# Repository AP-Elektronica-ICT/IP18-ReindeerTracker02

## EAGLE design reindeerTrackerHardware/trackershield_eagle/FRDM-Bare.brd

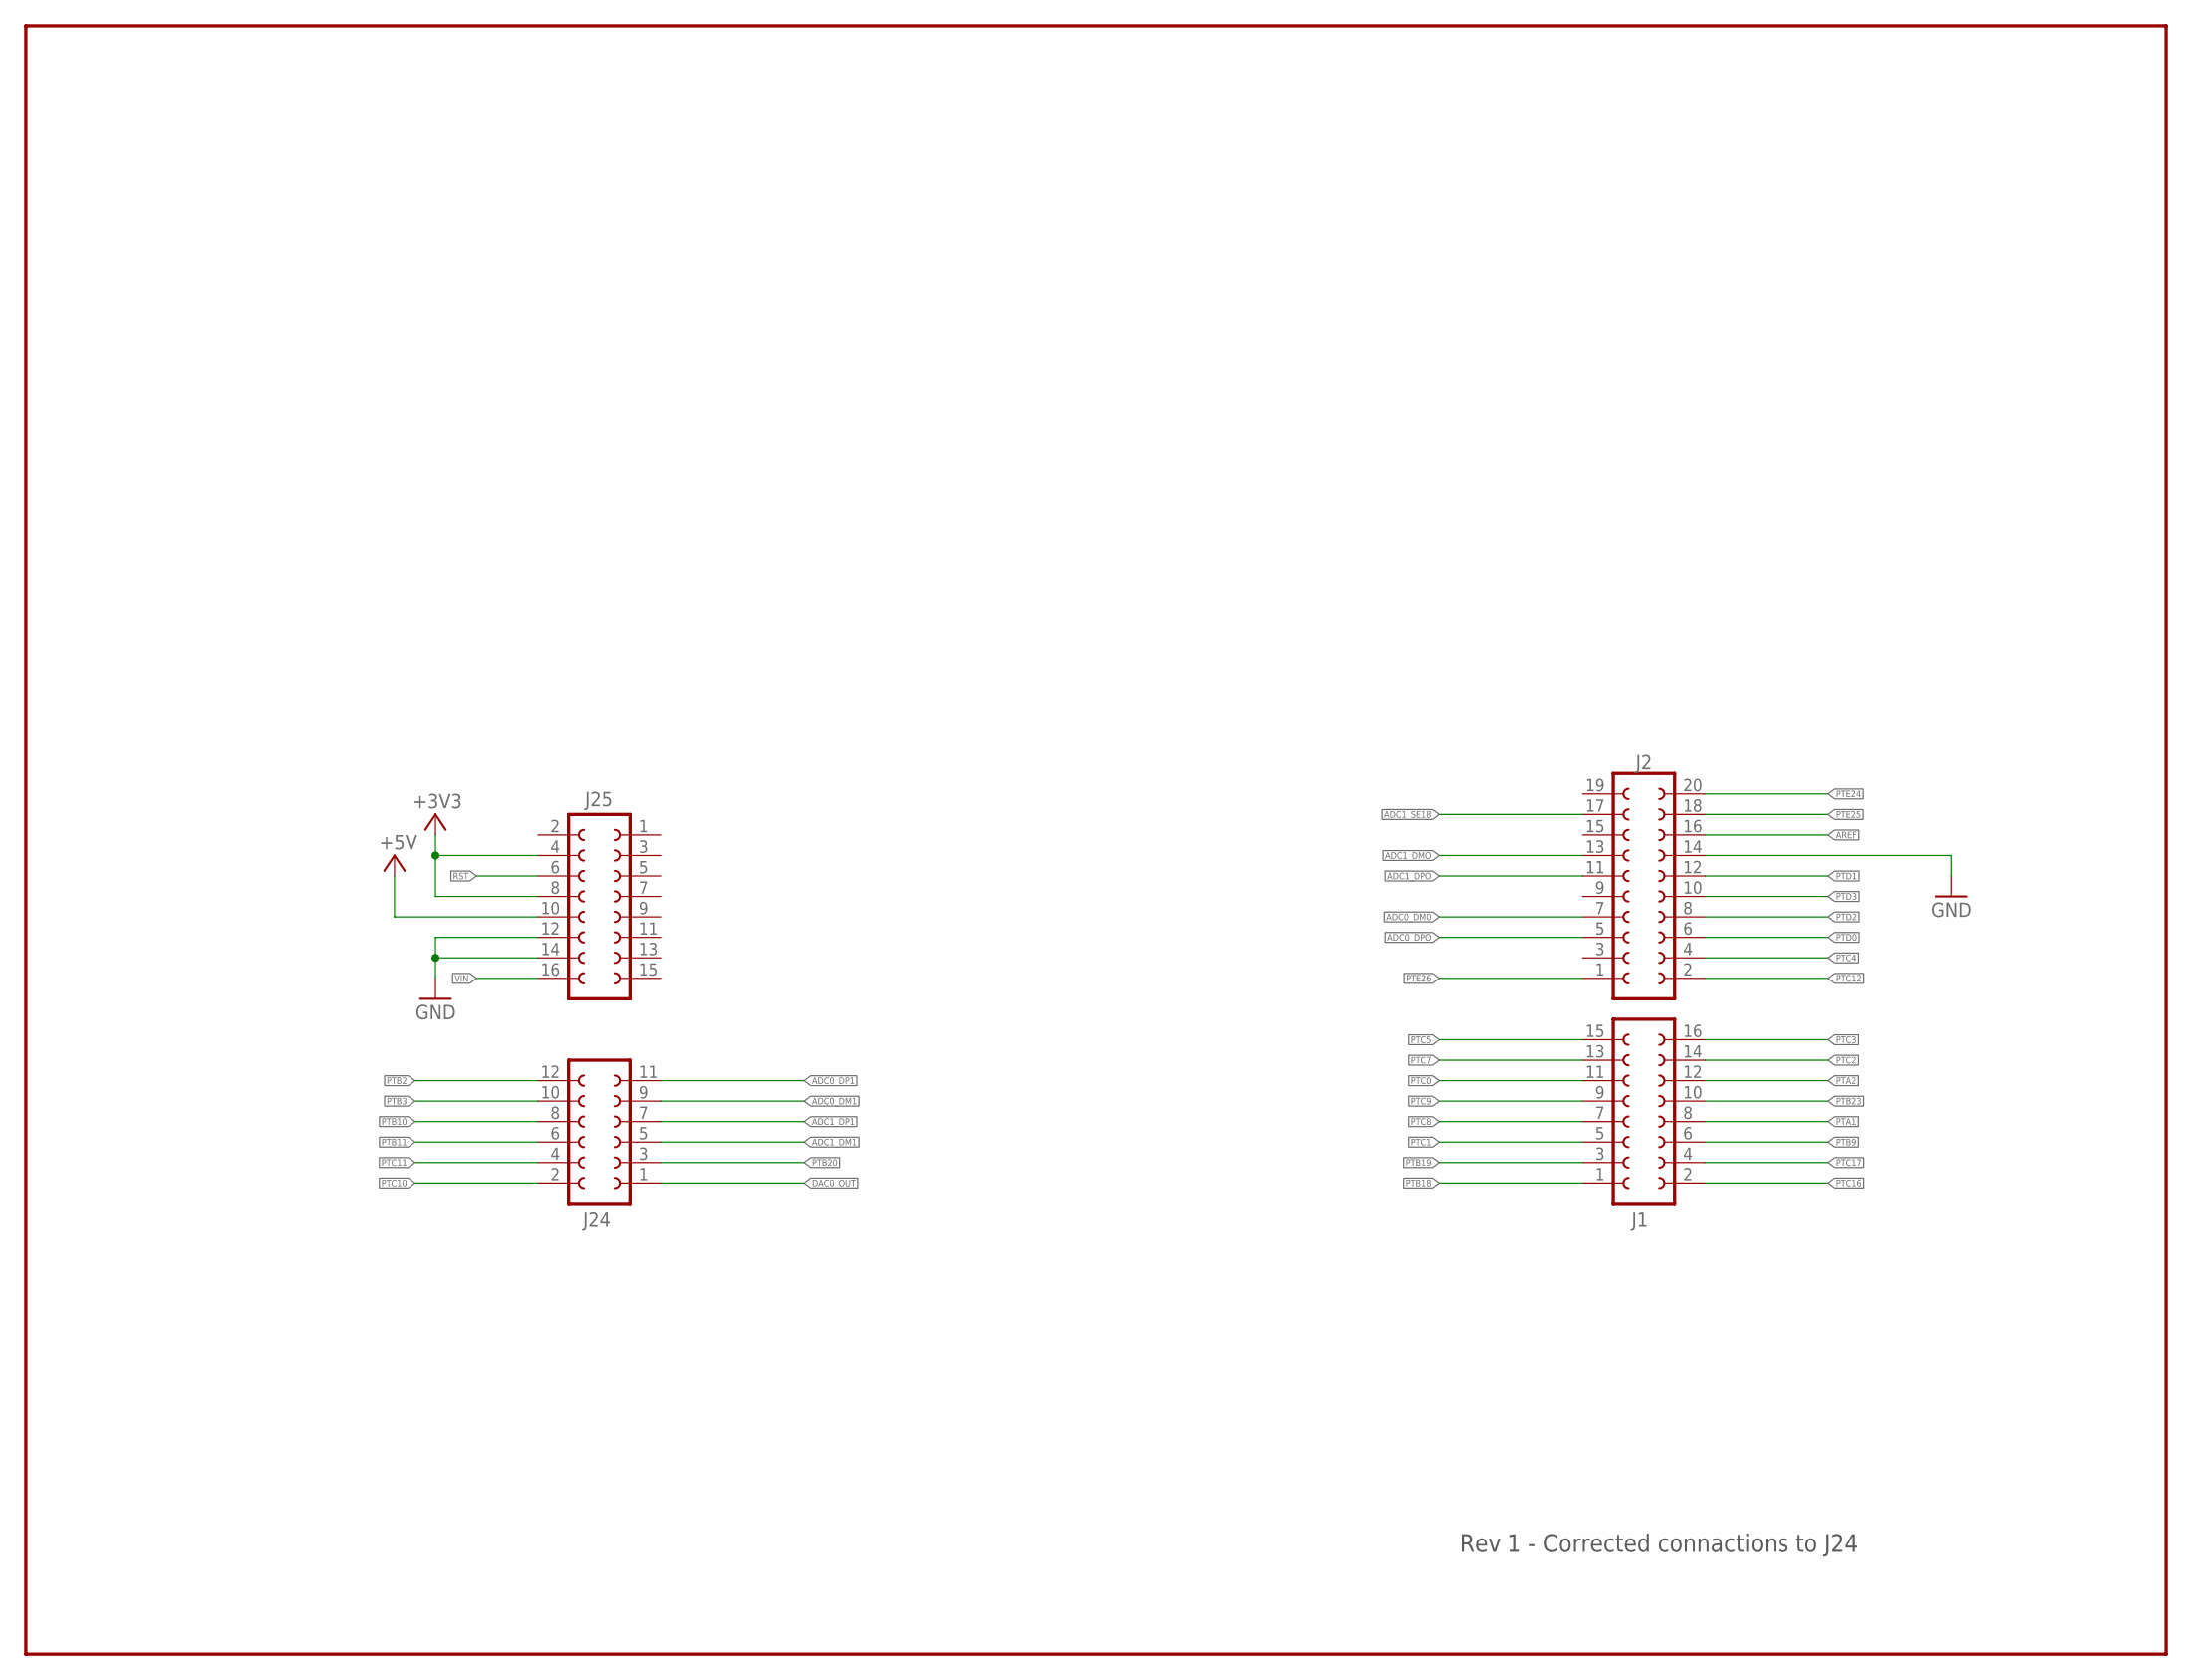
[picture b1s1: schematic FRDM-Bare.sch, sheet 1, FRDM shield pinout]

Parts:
J1, J25: FE08-2
J2: FE10-2
J24: FE06-2

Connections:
+3V3: J25.4, J25.8
+5V: J25.10
ADC0_DM0: J2.7
ADC0_DM1: J24.9
ADC0_DP1: J24.11
ADC0_DPO: J2.5
ADC1_DM1: J24.5
ADC1_DMO: J2.13
ADC1_DP1: J24.7
ADC1_DPO: J2.11
ADC1_SE18: J2.17
AREF: J2.16
DAC0_OUT: J24.1
GND: J2.14, J25.12, J25.14
PTA1: J1.8
PTA2: J1.12
PTB2: J24.12
PTB3: J24.10
PTB9: J1.6
PTB10: J24.8
PTB11: J24.6
PTB18: J1.1
PTB19: J1.3
PTB20: J24.3
PTB23: J1.10
PTC0: J1.11
PTC1: J1.5
PTC2: J1.14
PTC3: J1.16
PTC4: J2.4
PTC5: J1.15
PTC7: J1.13
PTC8: J1.7
PTC9: J1.9
PTC10: J24.2
PTC11: J24.4
PTC12: J2.2
PTC16: J1.2
PTC17: J1.4
PTD0: J2.6
PTD1: J2.12
PTD2: J2.8
PTD3: J2.10
PTE24: J2.20
PTE25: J2.18
PTE26: J2.1
RST: J25.6
VIN: J25.16

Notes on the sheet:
Rev 1 - Corrected connactions to J24

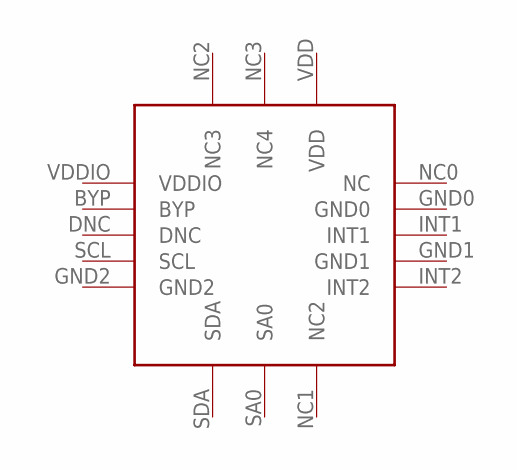
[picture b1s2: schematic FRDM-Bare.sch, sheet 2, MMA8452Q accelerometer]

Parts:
U$1: MMA8452Q; QFNPIN16

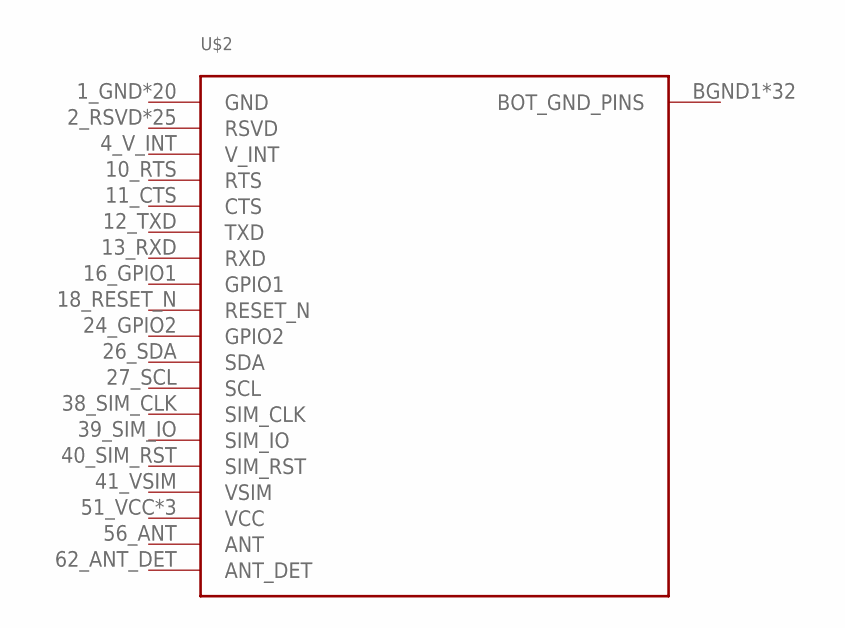
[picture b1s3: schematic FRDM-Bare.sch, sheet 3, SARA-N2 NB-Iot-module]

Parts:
U$2: SARA-N2

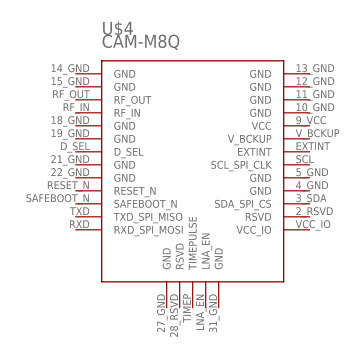
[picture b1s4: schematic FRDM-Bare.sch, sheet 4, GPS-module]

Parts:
U$4: CAM-M8Q

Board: 4 copper layers, 7 parts (0 on the bottom side), 2 nets, no tracks yet.

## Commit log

2018-02-07 Ionic app added
2018-02-07 Angular app added
2018-02-08 Firebase and Bootstrap added
2018-02-08 Serve error fixed
2018-02-08 make directory for hardware team and add datalogger device files
2018-02-08 make new folder reindeerlog for hardware team logging device source code
2018-02-09 make own files for i2c functions
2018-02-09 Updated accelerometer read
2018-02-09 Acc functions moved
2018-02-09 acc read function update
2018-02-09 XYZ axis acceleration reading and printing working
2018-02-09 merge
2018-02-09 acc function update
2018-02-09 paskaA2
2018-02-09 float workkia
2018-02-09 remove saatanan language settings
2018-02-09 start implementin adc
2018-02-11 start doing the SD card part. now can initialize card through SPI
2018-02-11 add FatFs library files
2018-02-12 put back driver files
2018-02-12 put back driver files, more files
2018-02-12 Resolving conflicts
2018-02-12 ADC functions added, working ADC
2018-02-12 Valid key code post call and backend models added
2018-02-12 gitignore added
2018-02-12 Multiple keys error handling and single key add API call added
2018-02-13 Get devices from user added
2018-02-13 Get specific device via deviceKey added
2018-02-13 Committing latest changes
2018-02-13 Return 5 logs with device details
2018-02-13 Get specific logs from device
2018-02-13 User device list only gives last log
2018-02-13 Querys updated, new log stored in first place of array
2018-02-13 Gitignore files/folders removed
2018-02-14 Accelerometer scaled around zero
2018-02-14 2 Accelerometers
2018-02-14 a c c e l b o y s
2018-02-14 SD card finally working yes
2018-02-14 Clean up code and add comments. Now logging reliably for 1,5hr at 25Hz rate
2018-02-15 Temperature sensing added and calibrated coursely
2018-02-15 small improvements
2018-02-16 Homepage website added
2018-02-19 add comments
2018-02-20 Updating
2018-02-20 change board clock settings to achieve lower power
2018-02-20 Interrupt function started, not working yet
2018-02-20 Some updates to SD card drivers to save power
2018-02-21 homepage added
2018-02-22 Routing module added
2018-02-22 basic design of the homescreen of the app
2018-02-22 Backend updated, device contains multiple users
2018-02-22 detail screen basics for app
2018-02-22 sensor service added
2018-02-22 Decreasing power consumpion of FRDM K64F board
2018-02-22 Manifacturers key add page on website added
2018-02-22 minor changes
2018-02-22 Maybe final commit for logger project. Clean up code. Fixed I2C wrong clock source frequency. Slow down data rate to 20hz. Improve sleep mode entering with prepare instruction. Revised external tempe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
2018-02-26 Add trackershield folder
2018-02-26 Version 2 started, acceleration interrupt enabled and working
2018-02-27 add board design files
2018-02-27 Frdm shield layout and components
2018-02-27 Timer counter reset by acceleration interrupt implemented - WIP
2018-02-27 Reindeer details add/update and device activation added on server
2018-02-27 Users can add devices to their list
2018-02-27 users devices display if device is activated
2018-02-27 added add, profile, delete, login and signup page and styled the login page
2018-03-01 Device details get request added to server
2018-03-02 Very low power mode activated
2018-03-02 add more components to trackershield
2018-03-02 make separate lbr file
2018-03-02 nothing useful
2018-03-02 library update
2018-03-02 nothing
2018-03-02 update ignore file to only track source folder
2018-03-02 update another gitignore
2018-03-02 maybe now fixed
2018-03-02 untrack shit..
2018-03-02 rework gitignore file to track ONLY SOURCE FOLDER
2018-03-03 add board folder back to tracked files
2018-03-04 IP11-35 + IP11-38 Detail page added
2018-03-04 activation moved to detail page' q
2018-03-05 detail page styling klaar
2018-03-08 added map to detail page
2018-03-08 login, sign up and password reset added
2018-03-08 Added basic layout to view reindeers of a user
2018-03-11 backand calls added to the app
2018-03-12 Yes.
2018-03-12 small change
2018-03-12 toimitko kiitos
2018-03-12 toimitko kiitos number 2
2018-03-12 paska git
2018-03-12 found the bug that disabled acc-wakeup
2018-03-13 fix ignore file again
2018-03-13 777 the ignore file
2018-03-13 paskaa
2018-03-13 pelastus uritus
2018-03-13 pelasta main
2018-03-13 pelastettu part 2
2018-03-13 New AT-func files added
2018-03-13 modify gitignore again to enable easier new project creation. now it tracks everything except the eclipse conf files(hope so)
2018-03-13 easier project creation still not working. now added .cproject and .project files to git, maybe that fixes it
2018-03-13 now add the files mentioned in previous commit...
2018-03-14 AT-commands communication functions implemented
2018-03-15 Two sided GPS communication by UART implemented
2018-03-15 Added login layout
2018-03-15 userdata on signup added
2018-03-16 Gps func implemented
2018-03-19 GPS-data parsed to strings
2018-03-19 profile page and delete page styled
2018-03-20 device add and qr scan completed
2018-03-21 UBX-messages sending and building CRC functions implemented
2018-03-22 GPS-location parsing and converting format implemented
2018-03-22 New ubx functions
2018-03-22 Nbiot and gps merger
2018-03-22 Initial log when user adds device
2018-03-22 some more gitignore head banging
2018-03-22 styled sign-up page
2018-03-22 sign up also adds email in database
2018-03-24 Clean up code and add comments, make interface for sending AT commands manually to module and optionally start tracking cycle
2018-03-24 Make UART2 work to communicate with GPS module. Now figured out UBX message sending and receiving. Can now view GPS output on console
2018-03-25 showing reindeers from database in delete page
2018-03-25 edit page added to detail screen
2018-03-25 Login redirects and navbar change on login added
2018-03-25 Added google maps to main code
2018-03-25 Device page and detail page backend calls added
2018-03-26 Local changes committed
2018-03-26 Make new system timer for better delay functions. Make accelerometer work. Make http packet function
2018-03-26 99iotasoy
2018-03-26 add old delay_ms
2018-03-26 Debugging GPS-print
2018-03-27 add MQTT function, fix GPS function lockup
2018-03-27 GPS location added to struct
2018-03-27 all merged
2018-03-27 local commit
2018-03-27 NBiot function can now assemble MQTT packet and send it
2018-03-27 Fix timing function causing lockup (do not put functions to .h file..), change string constants to proper type(now stored in program memory), change AT_send timeout
2018-03-28 Clean up code
2018-03-28 Now starts to search satellites, if coordinates found, sends them to server. Confirmed working once
2018-03-29 Gps location sending to server testing
2018-03-29 NBiot changes
2018-04-03 resend function
2018-04-03 jeee
2018-04-03 niimpaniin
2018-04-03 testi
2018-04-03 res dd
2018-04-03 moarpls
2018-04-03 add rfon rfoff command
2018-04-03 fix ignore files
2018-04-03 remove K64lib folder
2018-04-03 poroIoT project added and compiled
2018-04-03 joko
2018-04-03 KL17 modifications
2018-04-03 jopo
2018-04-03 make PCprint function
2018-04-04 add gps power control pin
2018-04-04 Protoboard tested code
2018-04-05 optimize power consumption
2018-04-06 optimize power
2018-04-06 timer and acc wakeup now workinggit add --all!
2018-04-06 remove release folder from git
2018-04-06 cleaned code
2018-04-06 small changes
2018-04-09 rtc functions implemented
2018-04-09 rtc functions version wan point wan
2018-04-09 modify ignore file
2018-04-09 rtc seconds working
2018-04-09 rtc, lptmr, acc interrupt all working somewhat
2018-04-09 api endpoint changed
2018-04-09 login added to app
2018-04-09 signup added to mobile app
2018-04-09 password reset added to mobile app
2018-04-09 don't show login page if authenticated
2018-04-09 set root page on login
2018-04-09 set roon redirect login
2018-04-10 kappa
2018-04-11 interrupts seemingly working, sends rtc timed report and detects dead reindeer and sends
2018-04-11 fix delay ms function too slow
2018-04-11 Notification receive and send added
2018-04-11 New server location origin added to cors
2018-04-12 add led blink to acc wakeup
2018-04-12 eimtnjrk
2018-04-13 Temperature and voltage measure
2018-04-15 average added
2018-04-15 Admin domain added
2018-04-15 Clean up code, make new file for debugging functions, add DEBUG_MODE define
2018-04-15 Merged temp and volt measure, cleaned up code, new file for debugging functions, interrupt freezing problem is now fixed
2018-04-16 tussen
2018-04-16 opening google maps
2018-04-17 implement GPS enable pin
2018-04-17 5kautta5
2018-04-17 Server ip address changed in app
2018-04-17 Profile page finished on app
2018-04-17 alive/death on homescreen of app and radius on map
2018-04-17 hardcoded button to go to maps
2018-04-17 Edit profile added
2018-04-17 map dynamic
2018-04-17 minor bug fix
2018-04-17 Birthdate removed from edit profile
2018-04-17 dynamic go to maps
2018-04-17 Google maps to last log added
2018-04-17 Loading modal added and user details change finished
2018-04-17 Page names changed
2018-04-17 Maps fixed
2018-04-18 voltage meeasure
2018-04-18 some debugging
2018-04-18 Filter added to mobile app
2018-04-18 Reduced amount of calls for user devices on mobile app
2018-04-18 Refresh added to mobile app
2018-04-18 Reset filter button added
2018-04-18 Line added when no devices are available
2018-04-18 Device list refreshes after logging in
2018-04-19 API endpoint changed on web app
2018-04-20 Device list display updated web app
2018-04-20 Remove device token added
2018-04-20 Profile page and profile edit added
2018-04-20 Icon added to new device button
2018-04-20 Device add replaced to modal
2018-04-20 Filter added to web app
2018-04-20 Device key changes from 6 to 5 digits
2018-04-20 Average returned from server
2018-04-20 Set current user directly after signup, bug fixed
2018-04-20 Directly go back after adding device if nothing changed
2018-04-20 Less http calls for devices on web app
2018-04-20 notifications added to server
2018-04-21 icon and splash screen
2018-04-21 Notifications marked if seen on website
2018-04-21 Notification added to beginning of list
2018-04-21 Notification delete added
2018-04-21 Won't mark as seen if there aren't any notifications unseen
2018-04-21 notification list added on mobile app
2018-04-21 Text when no notifications are available
2018-04-21 User invite added on server
2018-04-21 Invite bug fixed
2018-04-22 Invite by email, not uid
2018-04-22 Invites added to web app
2018-04-22 Reset device on web app when logging out
2018-04-22 Styling for inviting people
2018-04-22 Notification link added
2018-04-22 Subsribe to invite add
2018-04-22 Device notification bug fixed
2018-04-22 When first user adds device, add user to invites
2018-04-22 Activate removed from web app
2018-04-22 All bugs on web app fixed
2018-04-22 Send 404 when device does not exist
2018-04-22 Device token bug fixed
2018-04-23 styling
2018-04-23 Homepage changed
2018-04-23 Detail page layout updated
2018-04-23 Added dynamic google maps gps data link + change map types ft
2018-04-23 Added minor changes to sensor detail page
    expanded google maps map and made all sensor data dynamic
2018-04-23 Website notification refresh
2018-04-23 favicon added
2018-04-23 footer added
2018-04-23 play button added
2018-04-23 footer bug fix
2018-04-24 Layout website updated
2018-04-24 Profile link confirmation added
2018-04-24 added marker to map
2018-04-24 styling of marker on map
2018-04-24 date formatter added
